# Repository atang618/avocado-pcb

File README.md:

View this project on [CADLAB.io](https://cadlab.io/node/873). 

# avocado-pcb
PCB files for a smart actuator enabling chaining and providing precise positional control

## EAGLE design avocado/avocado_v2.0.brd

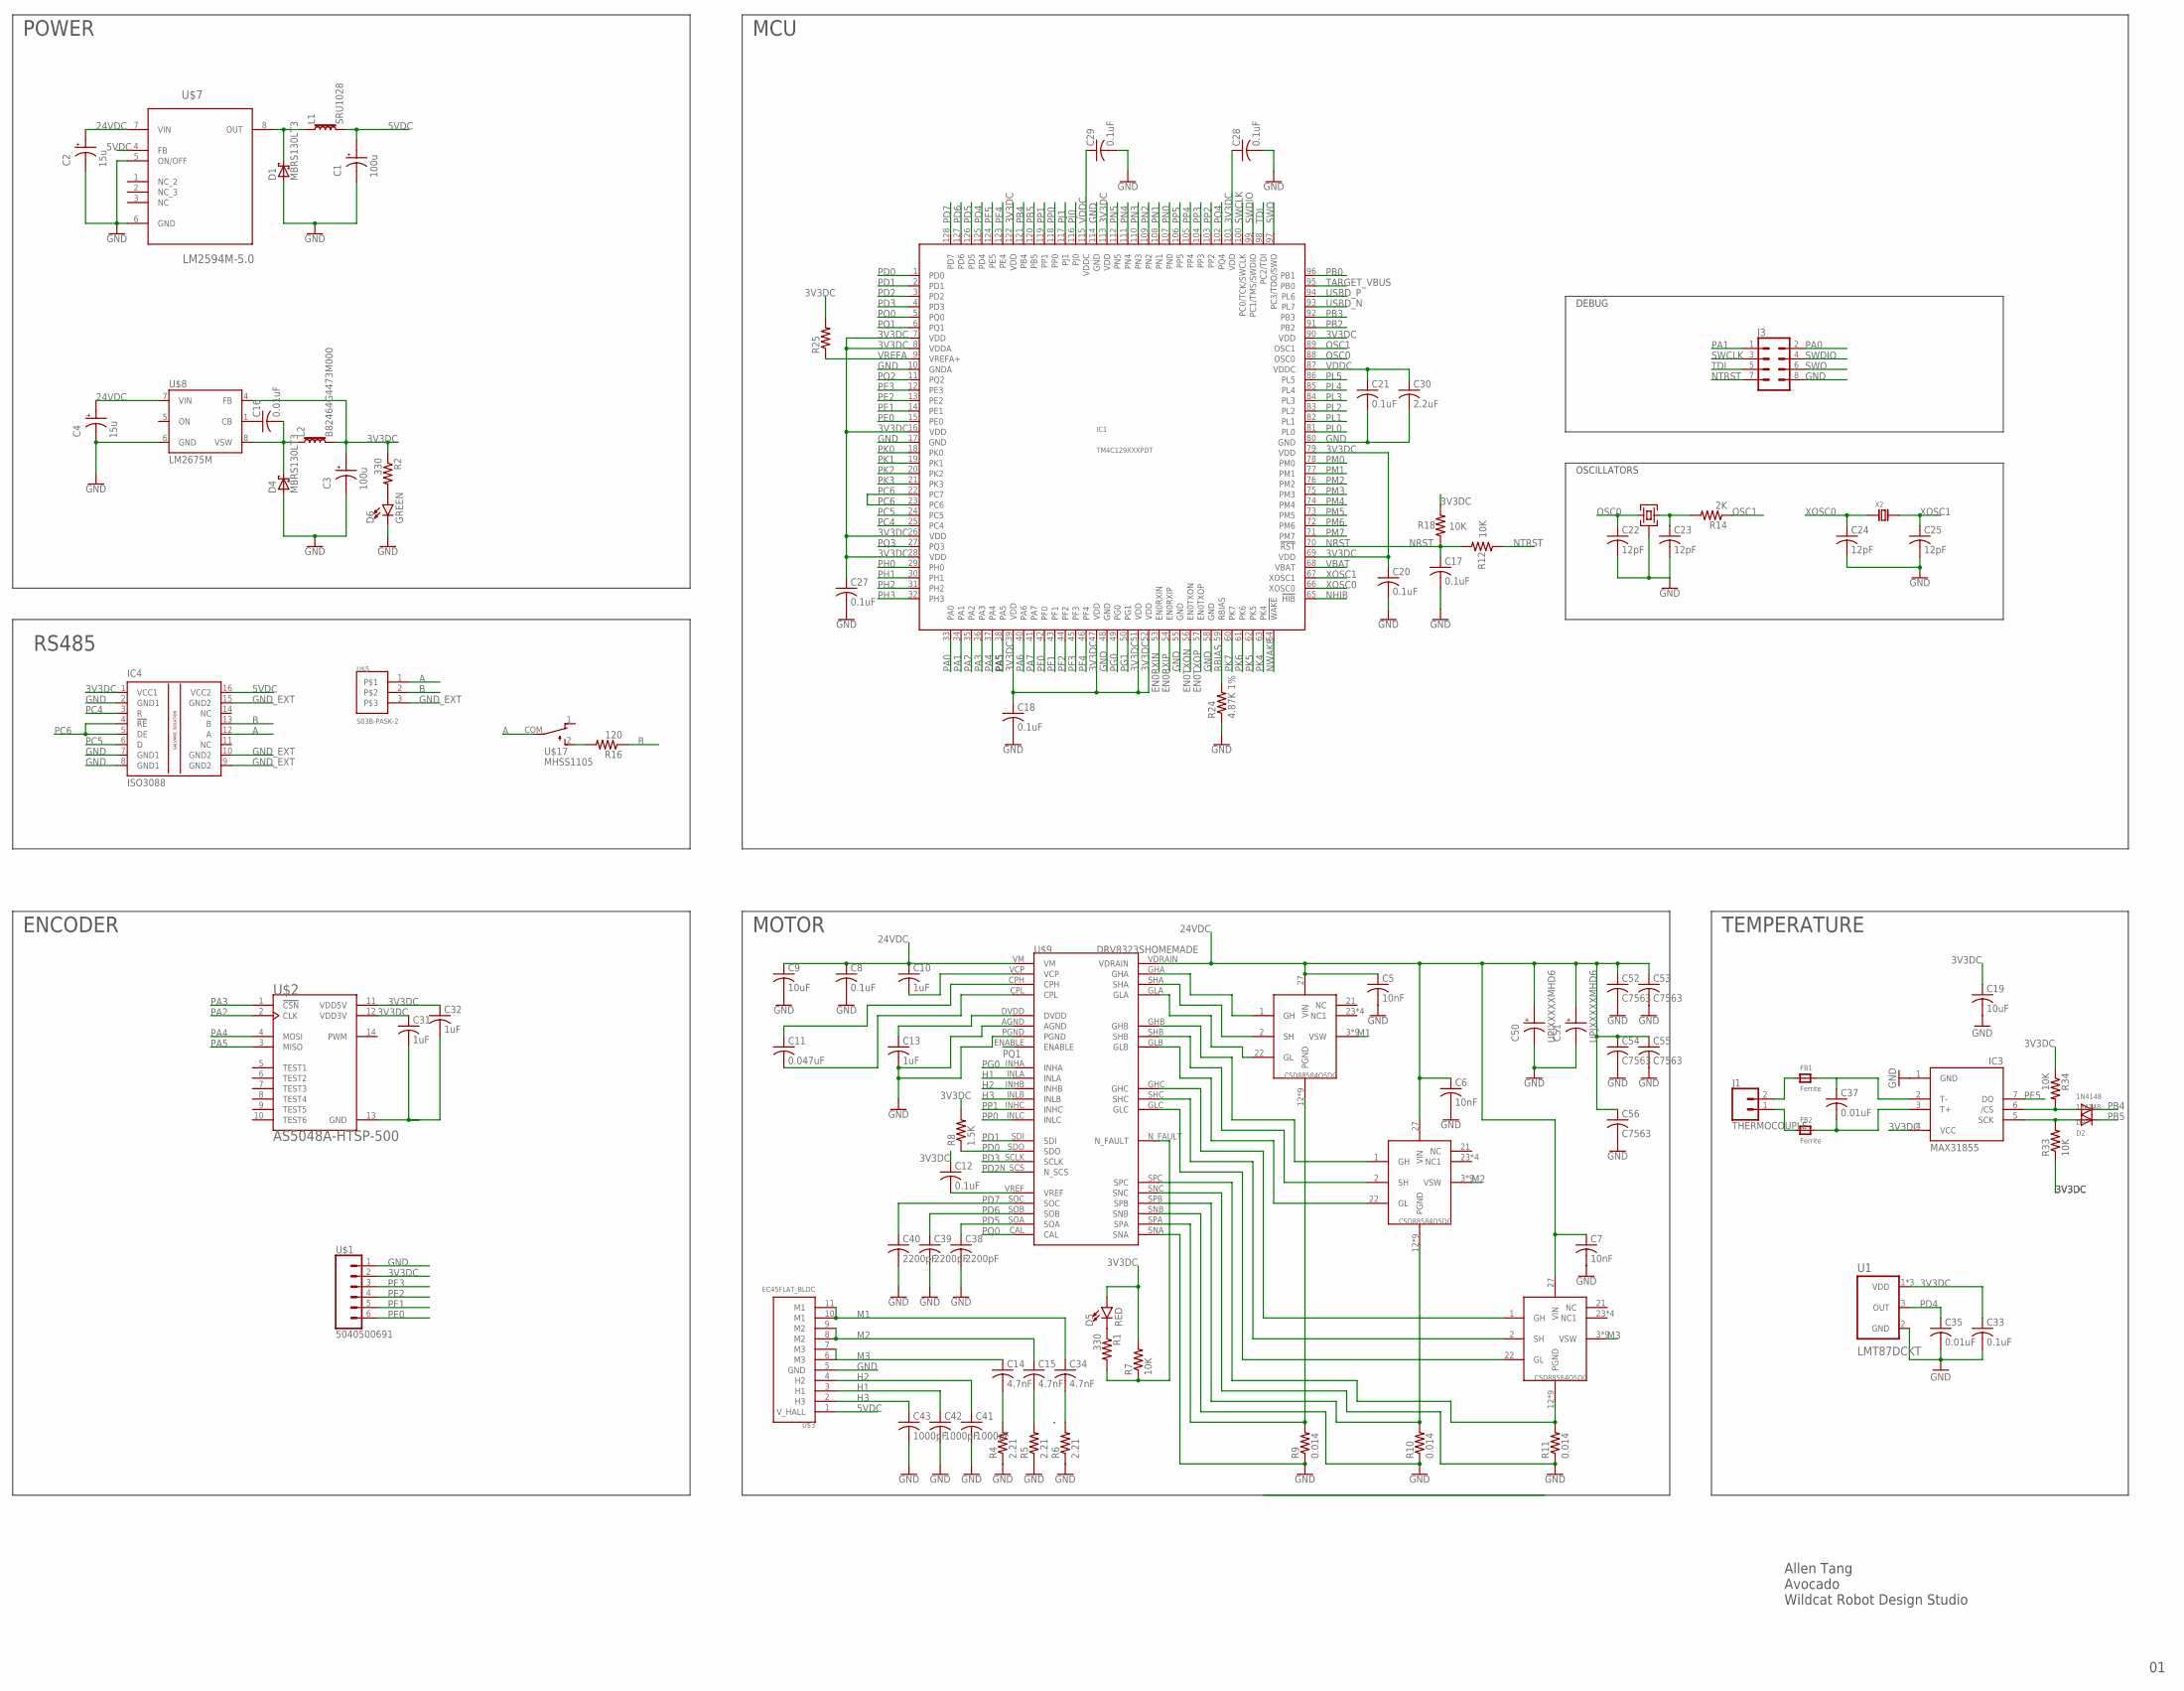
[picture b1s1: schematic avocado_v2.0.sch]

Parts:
C1, C3: 100u; 2917-D
C2, C4: 15u; 2917-D
C5, C6, C7: 10nF; C0402
C8, C12, C17, C18, C20, C21, C27, C28, C29, C33: 0.1uF; C0402
C9: 10uF; C0805
C10, C31, C32: 1uF; C0805
C11: 0.047uF; C0402
C13: 1uF; C0402
C14, C15, C34: 4.7nF; C0402
C16, C35, C37: 0.01uF; C0402
C19: 10uF; C0402
C22, C23, C24, C25: 12pF; C0402
C30: 2.2uF; C0402
C38, C39, C40: 2200pF; C0402
C41, C42, C43: 1000pF; C0402
C50, C51: UPJXXXXXMHD6
C52, C53, C54, C55, C56: C7563; 3025
D1, D4: MBRS130LT3; SMB
D2: 1n4148; SOD-323F
D3: 1N4148; SOD-323F
D5: RED; LED-0603
D6: GREEN; LED-0603
FB1, FB2: Ferrite; _0805
IC1: TM4C129XXXPDT; PDT_S-PQFP-G128
IC3: MAX31855; SO08
IC4: ISO3088; SOIC16
J1: THERMOCOUPLE; 2_SMP
J3: CONN_04X2; 2X4
L1: SRU1028
L2: B82464G4473M000
R1, R2: 330; R0402
R4, R5, R6: 2.21; R0805
R7, R12, R18, R33, R34: 10K; R0402
R8: 1.5K; R0402
R9, R10, R11: 0.014; R2512
R14: 2K; R0402
R16: 120; R0805
R24: 4.87K 1%; R0402
R25: R-US_R0402; R0402
U1: LMT87DCKT; SOT65P210X110-5N
U$1: 5040500691
U$2: AS5048A-HTSP-500; SOP65P640X120-14N
U$3: EC45FLAT_BLDC; 1MM-FPC-11PIN
U$4: NX3225GA
U$5: S03B-PASK-2
U$7: LM2594M-5.0; SOIC127P620X175-8N
U$8: LM2675M; SO08
U$9: DRV8323SHOMEMADE; DRV8323S
U$10, U$11, U$12: CSD88584Q5DC; MOSFET_CSD88599Q5DC
U$17: MHSS1105
X2: CRYSTAL-ABS07; ABRACON-ABS07-32.768KHZ

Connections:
3V3DC: C3.+ (A), C12.1, C18.1, C19.1, C20.1, C27.1, C28.1, C31.1, C32.1, C33.1, D5.A, IC1.7 (VDD), IC1.8 (VDDA), IC1.16 (VDD), IC1.26 (VDD), IC1.28 (VDD), IC1.39 (VDD), IC1.47 (VDD), IC1.51 (VDD), IC1.52 (VDD), IC1.69 (VDD), IC1.79 (VDD), IC1.90 (VDD), IC1.101 (VDD), IC1.113 (VDD), IC1.122 (VDD), IC3.4 (VCC), IC4.1 (VCC1), L2.2, R2.1, R7.2, R8.2, R18.2, R25.2, R33.1, R34.1, U1.1 (VDD), U1.4 (VDD), U1.5 (VDD), U$1.2, U$2.11 (VDD5V), U$2.12 (VDD3V), U$8.4 (FB)
5VDC: C1.+ (A), IC4.16 (VCC2), L1.2, U$3.1 (V_HALL), U$7.4 (FB)
24VDC: C2.+ (A), C4.+ (A), C5.1, C6.1, C7.1, C8.1, C9.1, C10.1, C50.+ (A), C51.+ (A), C52.P$1 (1), C53.P$1 (1), C54.P$1 (1), C55.P$1 (1), C56.P$1 (1), U$7.7 (VIN), U$8.7 (VIN), U$9.VDRAIN, U$9.VM, U$10.27 (VIN), U$11.27 (VIN), U$12.27 (VIN)
A: IC4.12 (A), U$5.1, U$17.COM
B: IC4.13 (B), R16.1, U$5.2
CS: D3.A, IC3.6 (/CS), R34.2
DVDD: C13.1, U$9.DVDD
EN0RXIN: IC1.53 (EN0RXIN)
EN0RXIP: IC1.54 (EN0RXIP)
EN0TXON: IC1.56 (EN0TXON)
EN0TXOP: IC1.57 (EN0TXOP)
GH1: U$9.GHA, U$12.1 (GH)
GH2: U$9.GHB, U$11.1 (GH)
GH3: U$9.GHC, U$10.1 (GH)
GL1: U$9.GLA, U$12.22 (GL)
GL2: U$9.GLB, U$11.22 (GL)
GL3: U$9.GLC, U$10.22 (GL)
GND: C1.- (C), C2.- (C), C3.- (C), C4.- (C), C5.2, C6.2, C7.2, C8.2, C9.2, C13.2, C17.2, C18.2, C19.2, C20.2, C21.2, C23.2, C24.2, C25.2, C27.2, C28.2, C29.2, C30.2, C31.2, C32.2, C33.2, C35.2, C38.2, C39.2, C40.2, C41.2, C42.2, C43.2, C50.- (C), C51.- (C), C52.P$2 (2), C53.P$2 (2), C54.P$2 (2), C55.P$2 (2), C56.P$2 (2), D1.A, D4.A, D6.C, IC1.10 (GNDA), IC1.17 (GND), IC1.48 (GND), IC1.55 (GND), IC1.58 (GND), IC1.80 (GND), IC1.114 (GND), IC3.1 (GND), IC4.2 (GND1), IC4.7 (GND1), IC4.8 (GND1), J3.8, R4.1, R5.1, R6.1, R9.1, R10.1, R11.1, R24.1, U1.2 (GND), U$1.1, U$2.13 (GND), U$3.5 (GND), U$7.5 (ON/OFF), U$7.6 (GND), U$8.6 (GND), U$9.AGND, U$9.PGND, U$9.SNA, U$9.SNB, U$9.SNC
GND_EXT: IC4.9 (GND2), IC4.10 (GND2), IC4.15 (GND2), U$5.3
H1: C42.1, U$3.3 (H1), U$9.INLA
H2: C41.1, U$3.4 (H2), U$9.INHB
H3: C43.1, U$3.2 (H3), U$9.INLB
ISENS1: R9.2, U$9.SPA, U$12.12 (PGND), U$12.13 (PGND), U$12.14 (PGND), U$12.15 (PGND), U$12.16 (PGND), U$12.17 (PGND), U$12.18 (PGND), U$12.19 (PGND), U$12.20 (PGND)
ISENS2: R10.2, U$9.SPB, U$11.12 (PGND), U$11.13 (PGND), U$11.14 (PGND), U$11.15 (PGND), U$11.16 (PGND), U$11.17 (PGND), U$11.18 (PGND), U$11.19 (PGND), U$11.20 (PGND)
ISENS3: R11.2, U$9.SPC, U$10.12 (PGND), U$10.13 (PGND), U$10.14 (PGND), U$10.15 (PGND), U$10.16 (PGND), U$10.17 (PGND), U$10.18 (PGND), U$10.19 (PGND), U$10.20 (PGND)
M1: C34.1, U$3.10 (M1), U$3.11 (M1), U$12.3 (VSW), U$12.4 (VSW), U$12.5 (VSW), U$12.6 (VSW), U$12.7 (VSW), U$12.8 (VSW), U$12.9 (VSW), U$12.10 (VSW), U$12.11 (VSW)
M2: C15.1, U$3.8 (M2), U$3.9 (M2), U$11.3 (VSW), U$11.4 (VSW), U$11.5 (VSW), U$11.6 (VSW), U$11.7 (VSW), U$11.8 (VSW), U$11.9 (VSW), U$11.10 (VSW), U$11.11 (VSW)
M3: C14.1, U$3.6 (M3), U$3.7 (M3), U$10.3 (VSW), U$10.4 (VSW), U$10.5 (VSW), U$10.6 (VSW), U$10.7 (VSW), U$10.8 (VSW), U$10.9 (VSW), U$10.10 (VSW), U$10.11 (VSW)
unnamed: C34.2, R6.2
unnamed: C10.2, U$9.VCP
unnamed: C11.1, U$9.CPH
unnamed: C16.1, U$8.1 (CB)
unnamed: C11.2, U$9.CPL
unnamed: D6.A, R2.2
unnamed: D5.C, R1.1
unnamed: FB1.1, J1.2
unnamed: C37.1, FB1.2, IC3.2 (T-)
unnamed: FB2.1, J1.1
unnamed: C37.2, FB2.2, IC3.3 (T+)
unnamed: C12.2, U$9.VREF
unnamed: R16.2, U$17.2
unnamed: D1.C, L1.1, U$7.8 (OUT)
unnamed: C16.2, D4.C, L2.1, U$8.8 (VSW)
unnamed: C14.2, R4.2
unnamed: C15.2, R5.2
unnamed: C22.2, U$4.P$2, U$4.P$4
unnamed: C23.1, R14.2, U$4.P$3
NFAULT: R1.2, R7.1, U$9.N_FAULT
NHIB: IC1.65 (!HIB)
NRST: C17.1, IC1.70 (!RST), R12.2, R18.1
NTRST: J3.7, R12.1
NWAKE: IC1.64 (!WAKE)
OSC0: C22.1, IC1.88 (OSC0), U$4.P$1
OSC1: IC1.89 (OSC1), R14.1
PA0: IC1.33 (PA0), J3.2
PA1: IC1.34 (PA1), J3.1
PA2: IC1.35 (PA2), U$2.2 (CLK)
PA3: IC1.36 (PA3), U$2.1 (!CSN)
PA4: IC1.37 (PA4), U$2.4 (MOSI)
PA5: IC1.38 (PA5), U$2.3 (MISO)
PA6: IC1.40 (PA6)
PA7: IC1.41 (PA7)
PB0: IC1.96 (PB1)
PB2: IC1.91 (PB2)
PB3: IC1.92 (PB3)
PB4: D3.C, IC1.121 (PB4)
PB5: D2.C, IC1.120 (PB5)
PC4: IC1.25 (PC4), IC4.3 (R)
PC5: IC1.24 (PC5), IC4.6 (D)
PC6: IC1.22 (PC7), IC1.23 (PC6), IC4.4 (!RE), IC4.5 (DE)
PD0: IC1.1 (PD0), R8.1, U$9.SDO
PD1: IC1.2 (PD1), U$9.SDI
PD2: IC1.3 (PD2), U$9.N_SCS
PD3: IC1.4 (PD3), U$9.SCLK
PD4: C35.1, IC1.125 (PD4), U1.3 (OUT)
PD5: C38.1, IC1.126 (PD5), U$9.SOA
PD6: C39.1, IC1.127 (PD6), U$9.SOB
PD7: C40.1, IC1.128 (PD7), U$9.SOC
PE0: IC1.15 (PE0), U$1.6
PE1: IC1.14 (PE1), U$1.5
PE2: IC1.13 (PE2), U$1.4
PE3: IC1.12 (PE3), U$1.3
PE4: IC1.123 (PE4)
PE5: IC1.124 (PE5), IC3.7 (DO)
PF0: IC1.42 (PF0)
PF1: IC1.43 (PF1)
PF2: IC1.44 (PF2)
PF3: IC1.45 (PF3)
PF4: IC1.46 (PF4)
PG0: IC1.49 (PG0), U$9.INHA
PG1: IC1.50 (PG1)
PH0: IC1.29 (PH0)
PH1: IC1.30 (PH1)
PH2: IC1.31 (PH2)
PH3: IC1.32 (PH3)
PJ0: IC1.116 (PJ0)
PJ1: IC1.117 (PJ1)
PK0: IC1.18 (PK0)
PK1: IC1.19 (PK1)
PK2: IC1.20 (PK2)
PK3: IC1.21 (PK3)
PK4: IC1.63 (PK4)
PK5: IC1.62 (PK5)
PK6: IC1.61 (PK6)
PK7: IC1.60 (PK7)
PL0: IC1.81 (PL0)
PL1: IC1.82 (PL1)
PL2: IC1.83 (PL2)
PL3: IC1.84 (PL3)
PL4: IC1.85 (PL4)
PL5: IC1.86 (PL5)
PM0: IC1.78 (PM0)
PM1: IC1.77 (PM1)
PM2: IC1.76 (PM2)
PM3: IC1.75 (PM3)
PM4: IC1.74 (PM4)
PM5: IC1.73 (PM5)
PM6: IC1.72 (PM6)
PM7: IC1.71 (PM7)
PN0: IC1.107 (PN0)
PN1: IC1.108 (PN1)
PN2: IC1.109 (PN2)
PN3: IC1.110 (PN3)
PN4: IC1.111 (PN4)
PN5: IC1.112 (PN5)
PP0: IC1.118 (PP0), U$9.INLC
PP1: IC1.119 (PP1), U$9.INHC
PP2: IC1.103 (PP2)
PP3: IC1.104 (PP3)
PP4: IC1.105 (PP4)
PP5: IC1.106 (PP5)
PQ0: IC1.5 (PQ0), U$9.CAL
PQ1: IC1.6 (PQ1), U$9.ENABLE
PQ2: IC1.11 (PQ2)
PQ3: IC1.27 (PQ3)
PQ4: IC1.102 (PQ4)
RBIAS: IC1.59 (RBIAS), R24.2
SCK: D2.A, IC3.5 (SCK), R33.2
SH1: U$9.SHA, U$12.2 (SH)
SH2: U$9.SHB, U$11.2 (SH)
SH3: U$9.SHC, U$10.2 (SH)
SWCLK: IC1.100 (PC0/TCK/SWCLK), J3.3
SWDIO: IC1.99 (PC1/TMS/SWDIO), J3.4
SWO: IC1.97 (PC3/TDO/SWO), J3.6
TARGET_VBUS: IC1.95 (PB0)
TDI: IC1.98 (PC2/TDI), J3.5
USBD_N: IC1.93 (PL7)
USBD_P: IC1.94 (PL6)
VBAT: IC1.68 (VBAT)
VDDC: C21.1, C29.1, C30.1, IC1.87 (VDDC), IC1.115 (VDDC)
VREFA: IC1.9 (VREFA+), R25.1
XOSC0: C24.1, IC1.66 (XOSC0), X2.P$1
XOSC1: C25.1, IC1.67 (XOSC1), X2.P$2

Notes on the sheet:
RS485
POWER
MCU
OSCILLATORS
Allen Tang Avocado Wildcat Robot Design Studio
ENCODER
MOTOR
TEMPERATURE
DEBUG

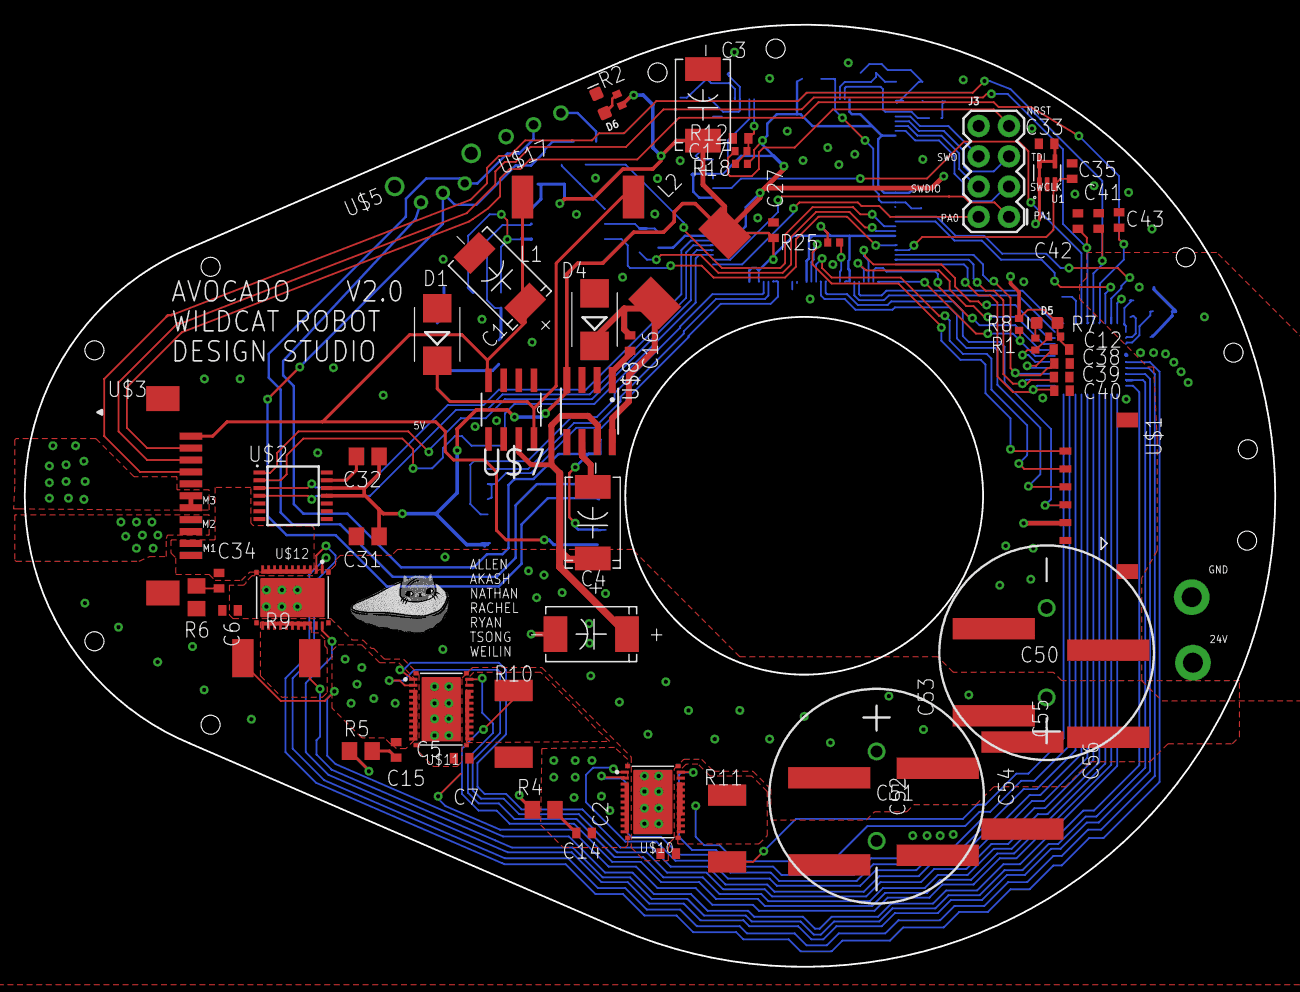
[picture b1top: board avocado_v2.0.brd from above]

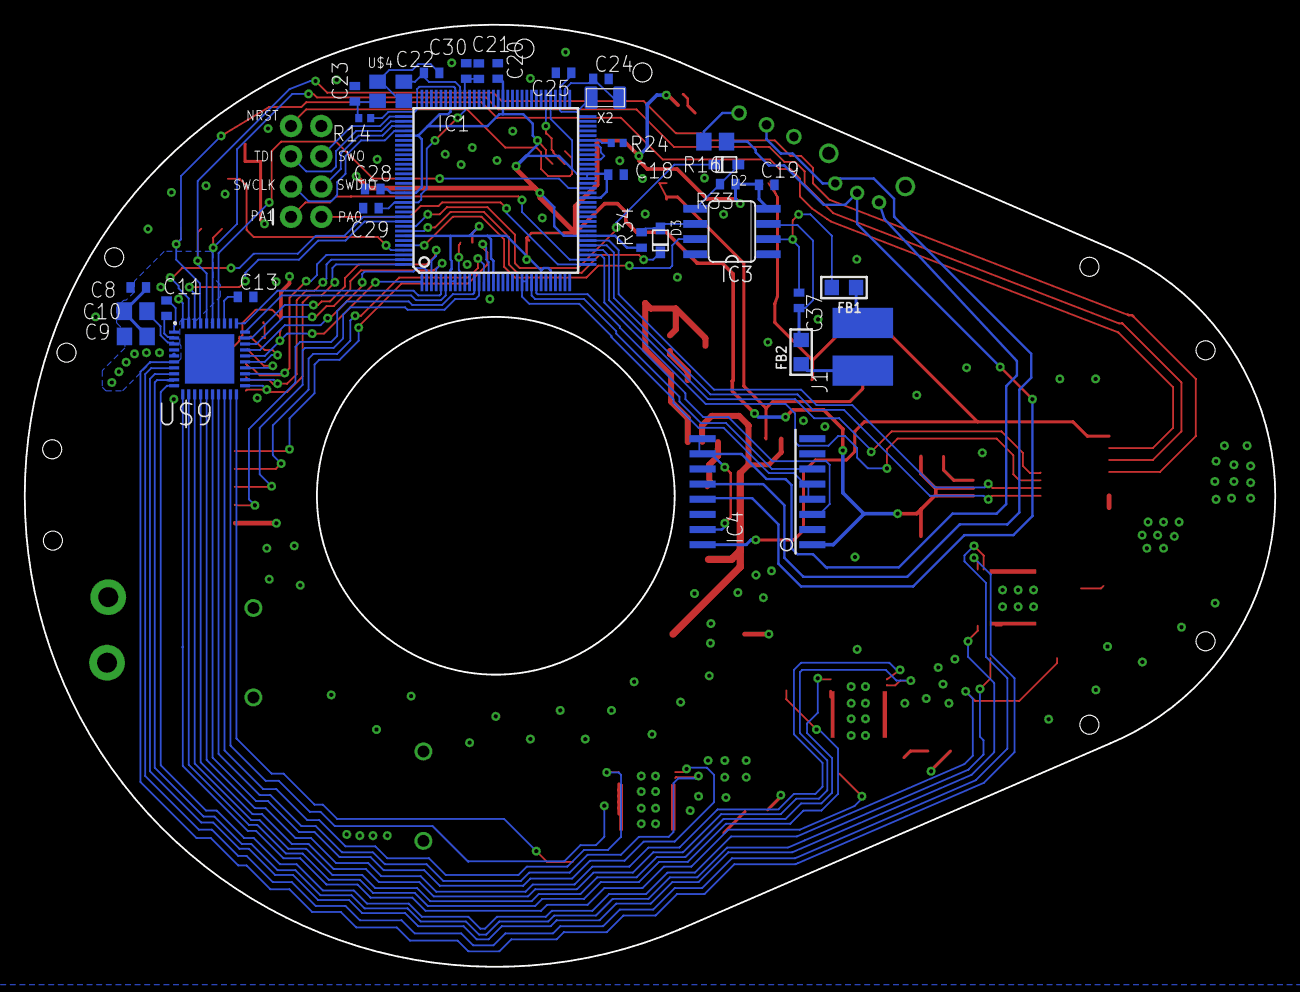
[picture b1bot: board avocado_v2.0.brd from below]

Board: 4 copper layers, 104.9 x 79.0 mm, 95 parts (33 on the bottom side), 90 nets.

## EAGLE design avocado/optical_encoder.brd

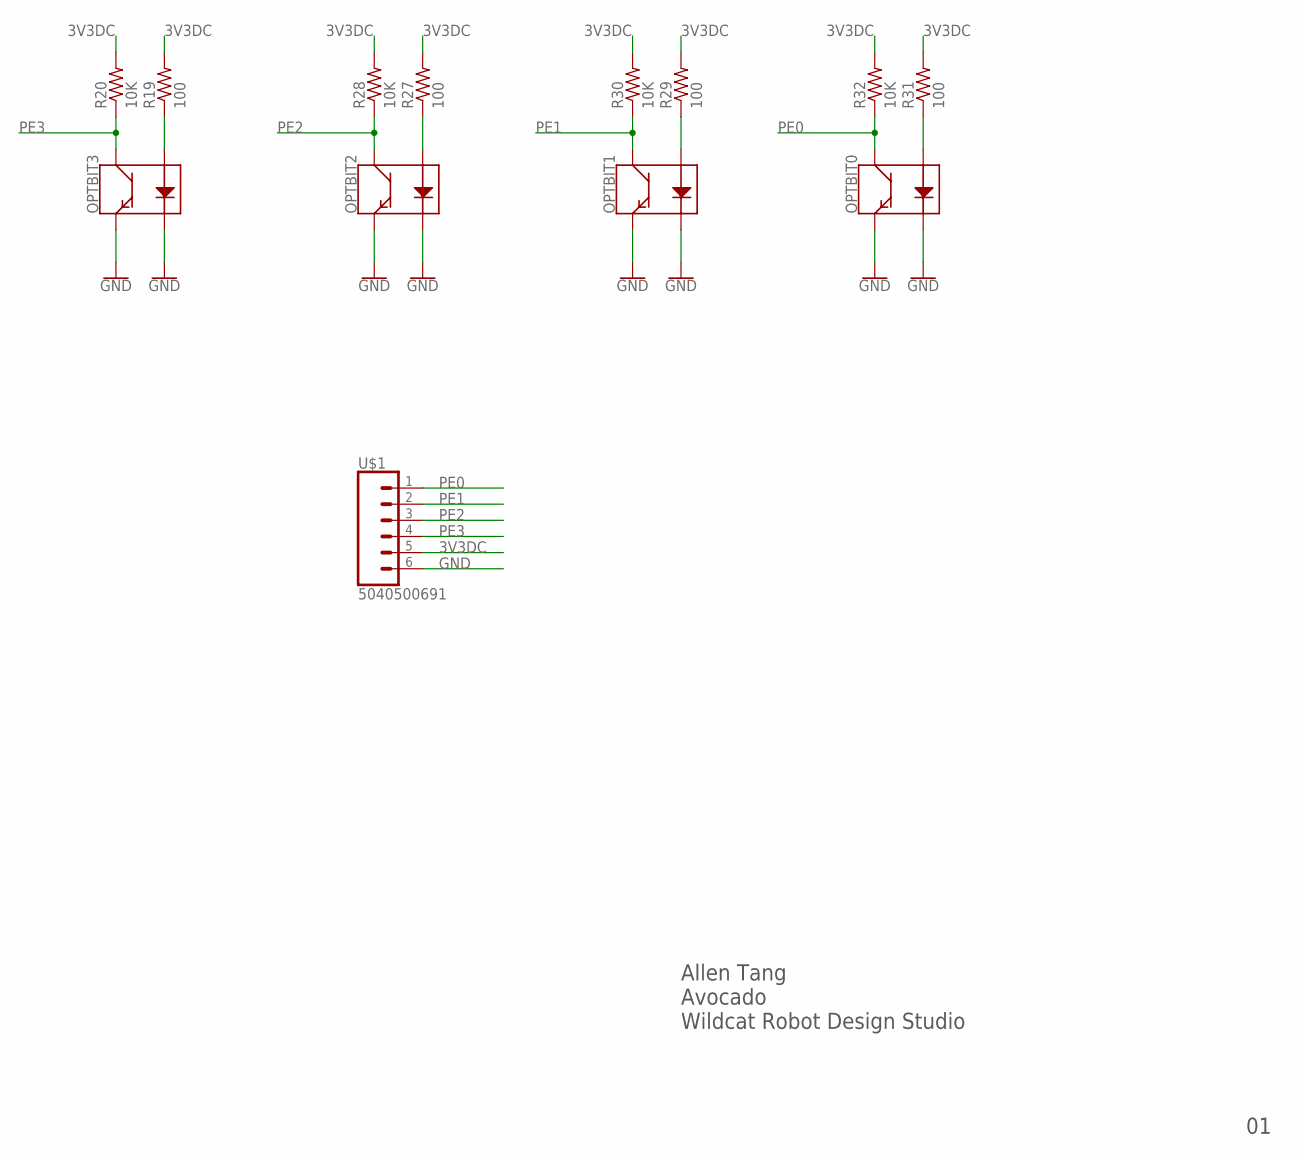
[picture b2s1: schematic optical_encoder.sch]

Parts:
OPTBIT0, OPTBIT1, OPTBIT2, OPTBIT3: QRE1113
R19, R27, R29, R31: 100; R0402
R20, R28, R30, R32: 10K; R0402
U$1: 5040500691

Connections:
3V3DC: R19.2, R20.2, R27.2, R28.2, R29.2, R30.2, R31.2, R32.2, U$1.5
GND: OPTBIT0.2 (K), OPTBIT0.4 (E), OPTBIT1.2 (K), OPTBIT1.4 (E), OPTBIT2.2 (K), OPTBIT2.4 (E), OPTBIT3.2 (K), OPTBIT3.4 (E), U$1.6
unnamed: OPTBIT3.1 (A), R19.1
unnamed: OPTBIT2.1 (A), R27.1
unnamed: OPTBIT1.1 (A), R29.1
unnamed: OPTBIT0.1 (A), R31.1
PE0: OPTBIT0.3 (C), R32.1, U$1.1
PE1: OPTBIT1.3 (C), R30.1, U$1.2
PE2: OPTBIT2.3 (C), R28.1, U$1.3
PE3: OPTBIT3.3 (C), R20.1, U$1.4

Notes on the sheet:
Allen Tang Avocado Wildcat Robot Design Studio

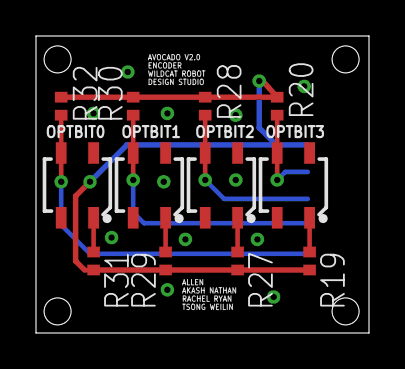
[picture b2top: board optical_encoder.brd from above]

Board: 2 copper layers, 18.5 x 16.5 mm, 13 parts (1 on the bottom side), 10 nets.

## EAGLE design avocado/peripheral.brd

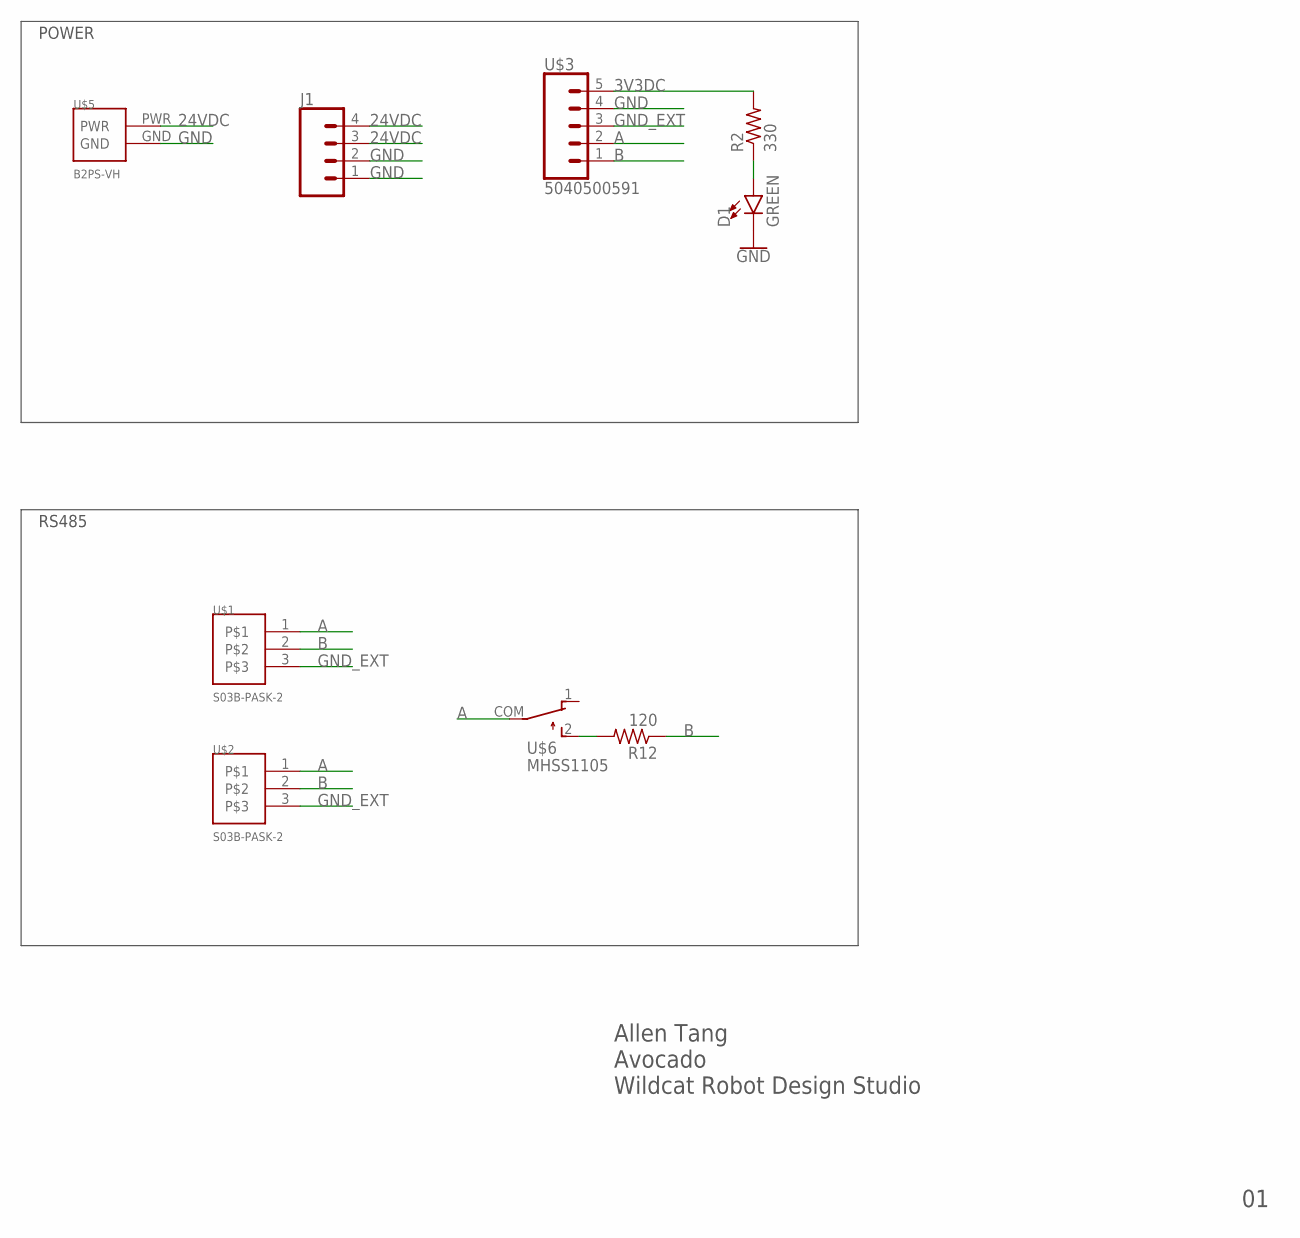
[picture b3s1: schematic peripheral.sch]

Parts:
D1: GREEN; LED-0603
J1: CONN_04; 1X04
R2: 330; R0805
R12: 120; R0805
U$1, U$2: S03B-PASK-2
U$3: 5040500591
U$5: B2PS-VH
U$6: MHSS1105

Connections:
3V3DC: R2.2, U$3.5
24VDC: J1.3, J1.4, U$5.PWR
A: U$1.1, U$2.1, U$3.2, U$6.COM
B: R12.1, U$1.2, U$2.2, U$3.1
GND: D1.C, J1.1, J1.2, U$3.4, U$5.GND
GND_EXT: U$1.3, U$2.3, U$3.3
unnamed: D1.A, R2.1
unnamed: R12.2, U$6.2

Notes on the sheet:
Allen Tang Avocado Wildcat Robot Design Studio
POWER
RS485

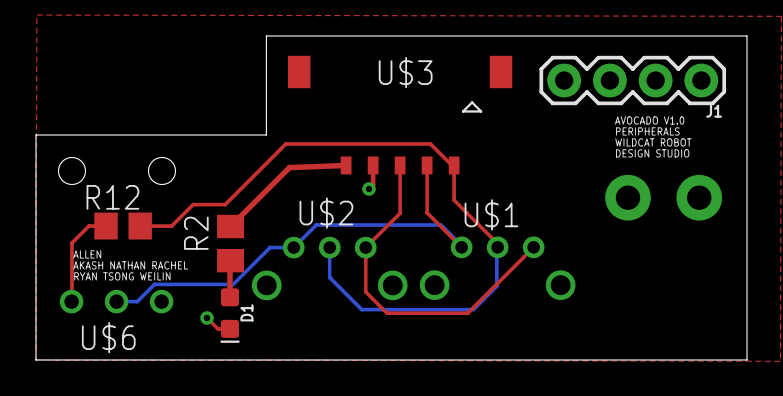
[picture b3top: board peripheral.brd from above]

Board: 2 copper layers, 39.5 x 18.0 mm, 9 parts (0 on the bottom side), 8 nets.

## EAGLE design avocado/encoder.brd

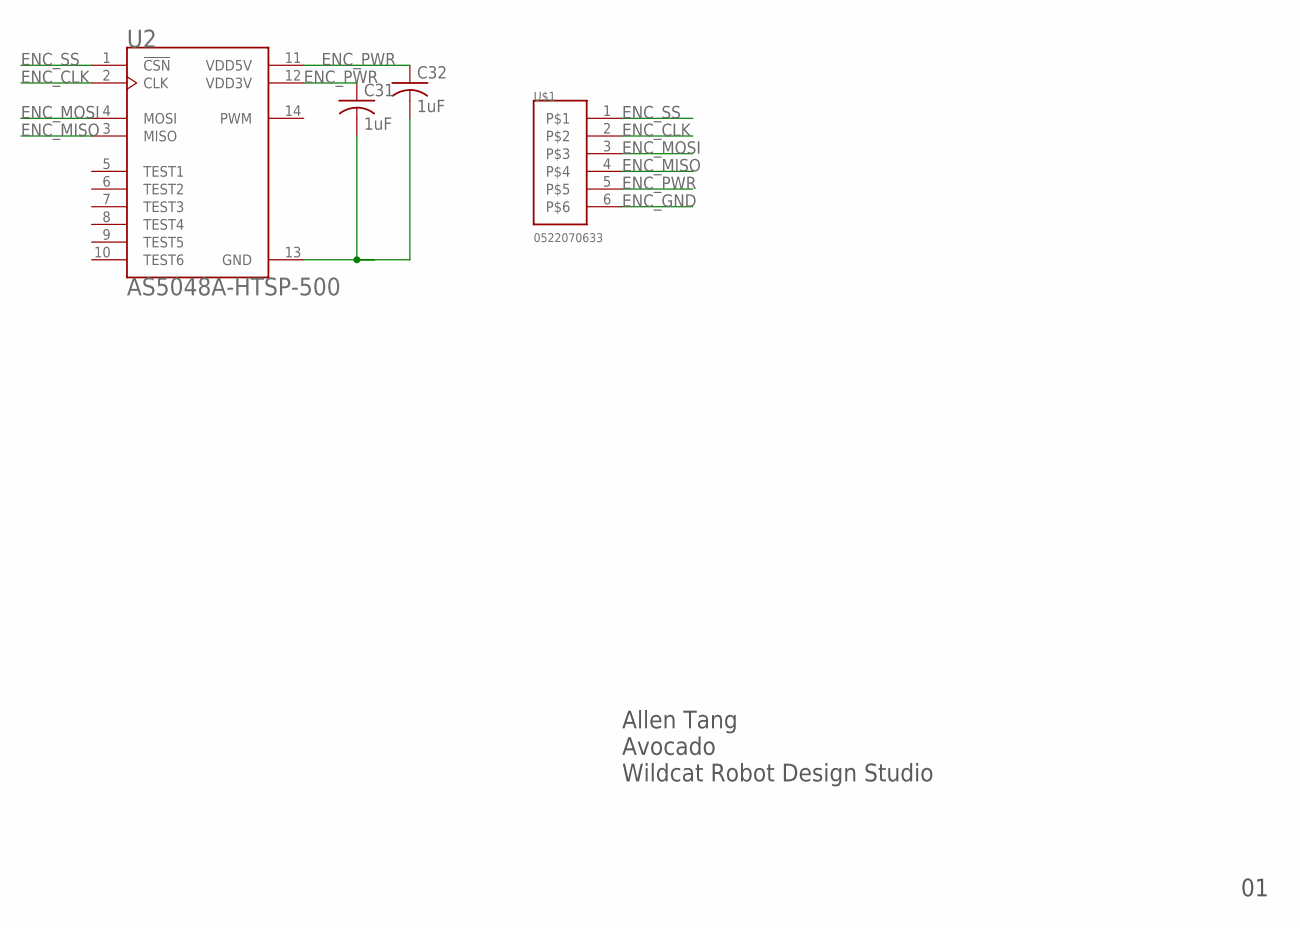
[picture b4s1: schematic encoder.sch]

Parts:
C31, C32: 1uF; C0805
U2: AS5048A-HTSP-500; SOP65P640X120-14N
U$1: 0522070633; 1MM-FPC-6PIN

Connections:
ENC_CLK: U2.2 (CLK), U$1.2
ENC_GND: C31.2, C32.2, U2.13 (GND), U$1.6
ENC_MISO: U2.3 (MISO), U$1.4
ENC_MOSI: U2.4 (MOSI), U$1.3
ENC_PWR: C31.1, C32.1, U2.11 (VDD5V), U2.12 (VDD3V), U$1.5
ENC_SS: U2.1 (!CSN), U$1.1

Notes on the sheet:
Allen Tang Avocado Wildcat Robot Design Studio

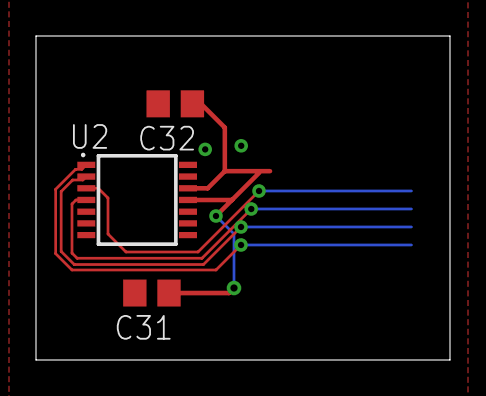
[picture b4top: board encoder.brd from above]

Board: 2 copper layers, 23.0 x 18.0 mm, 4 parts (1 on the bottom side), 6 nets.

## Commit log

2018-02-07 initial wiring of motor driver
2018-02-07 finished wiring MCU
2018-02-07 fixed the title block
2018-04-10 added power and encoder block
2018-04-12 updated motor block, power and temperature
2018-04-12 Backlink to CADLAB.io has been added.
2018-04-12 cleaned up the parts for the schematic
2018-04-14 finished adding parts for motor
2018-04-15 started board layout
2018-04-15 made significant routing progress
2018-04-16 started Motor traces
2018-04-17 fixed all airwires, still need to fix DRC
2018-04-18 expanded power and motor traces
2018-04-19 redesigned FET and Cap orientation
2018-04-19 finished DRC and silk for version 1
2018-04-19 added version and gerber files
2018-04-19 design that was ordered in first PCB run
2018-04-20 removed blind vias and generated new Gerber files
2018-04-22 new gerber files and updated peripheral/main board
2018-04-24 updated encoder board size
2018-04-24 modified peripheral board size
2018-04-24 added mounting holes on peripheral board
2018-04-24 updated encoder and peripheral
2018-05-05 added v2.0 of the avocado main pcb
2018-05-05 added mounting holes to main pcb
2018-05-05 added new optical encoder board
2018-05-08 added power connector board
2018-05-08 version 2 of the avocado pcb finished
2018-05-09 finalized optical encoder and power connector boards
2018-05-17 latest gerbers and main pcb design

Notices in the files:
parts and their libraries:
SparkFun-LED: Licensing: Creative Commons ShareAlike 4.0 International - https://creativecommons.org/licenses/by-sa/4.0
